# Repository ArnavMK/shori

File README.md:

**Shori PCB Layout:**

### What is this project?

Shori is a custom digital fx processor pcb for electric guitars. This is the heart of the modular project i am building called Wave forge (a solid state guitar amplifier )
And this is the first revision of the board!

This project comprises of three different printed circuit boards
1. Main power amp, preamp and I/O board: Shoyu (To be started)
2. The Digital FX processor: Shori (Rev 1 finished) 
3. The Screen controller board: Gamen (to be started)

here is the link for waveforge: [Here](https://github.com/ArnavMK/WaveForge)

### How to use it?

This is just rev 1 and is not manufactured yet, but this is a part of much larger multi board system and hence it needs to be connected to the other boards, through the two main connectors
The main ribbon connector for power and guitar audio from Shoyu. And the JST connector for the UART communication between the screen and shori. The screen has UI for controlling the parameters the digital fx like wet time modulation for delay and chorus. The screen will also have a waveform visualizer which is also be generated through shori.

### Why I made it

I have been playing electric for the past 11 years and never thought to build my own amp untill i met a friend profound in electronics and hardware design who inspired me into making my own. This board is the first step into putting a massive dent in WaveForge and i cant wait to finish it. Linked posts do not know what's coming for them.

I am pretty much nuking half the board for rev 2 now, after some peer roasting and friendly fire

### Project Pictures

There is no 3D encloser cad for shori yet! because that is the amp. Layout and 3D cad given on top of this page.

---

### Bill of Materials (BOM) FOR REV 1 ONLY !

This bom does not include the extra amount for each component, this is for only one shori board with perfect amount of compoenents!

*(A full `shori.csv` is also included in the root directory of this repository).*

| Component | Part Number | Quantity | Link | Cost (euro) |
| --- | --- | --- | --- | --- |
| Microcontroller | STM32F405RGT6 | 1 | [Link](https://www.digikey.ie/en/products/detail/stmicroelectronics/STM32F405RGT6/2754208) | 10.4 |
| Audio Codec | TI PCM3060 | 1 | [Link](https://www.digikey.com/en/models/1900019?tab=snapmagic) | 5.78 |
| Dual Audio Op-Amp | NE5532 | 1 | [Link](https://www.digikey.com/en/products/detail/texas-instruments/NE5532DR/499499) | 0.43 |
| Crystal Oscillator | 7M-25.000MAAE-T | 1 | [Link](https://www.digikey.ie/en/products/detail/txc-corporation/7M-25-000MAAE-T/3674351) | 0.59 |
| 3.3V LDO Regulator | AP2112K-3.3 | 1 | [Link](https://www.digikey.ie/en/products/detail/diodes-incorporated/ap2112k-3-3trg1/4470746) | 0.22 |
| 0805 capacitors (10uF) | 0805B475K160CC | 6 | [Link](https://www.digikey.com/en/products/detail/nextgen-components/0805B475K160CC/22601960?s=N4IgjCBcpgLFoDGUBmBDANgZwKYBoQB7KAbXAAYAOAdlgCYQBdAgBwBcoQBlNgJwEsAdgHMQAXwJhqCEMkjps%2BIqRD06sMAFYmrDpG58hoiSDqaG0Waky4CxSGXV0AnGEo6Q7TjwEjxk50pnGTkFW2UHEHImEzpyWGDLUJslezJyADowAAIAVoAxEAJYDOo8wslyco8vfQBVQX42AHkUAFkcNCwAV14cfxAAWngk60U7FVcANnJpRhNB7VH5FInIiHmxMSA) | 0.34 |
| 0805 capacitors (100nF) | 0805B104K500BD | 11 | [Link](https://www.digikey.com/en/products/detail/nextgen-components/0805B104K500BD/15776052) | 0.078 |
| Custom PCB | 4-Layer FR4 | 5 | [Link](https://jlcpcb.com/) | 6.02 |
| JLCPCB shipping | DHL to ireland | - | [Link](https://jlcpcb.com/) | 26.95 |
| 0805 capacitors (2.2uF) | CL21B225KAFNNNE | 2 | [Link](https://www.digikey.com/en/products/detail/samsung-electro-mechanics/CL21B225KAFNNNE/3888612) | 0.12 |
| 0805 capacitors (1uF) | CL21B105KAFNNNE | 3 | [Link](https://www.digikey.com/en/products/detail/samsung-electro-mechanics/CL21B105KAFNNNE/3886724) | 0.10 |
| 0805 resistors (10K) | CR0805-FX-1002ELF | 7 | [Link](https://www.digikey.com/en/products/detail/bourns-inc/CR0805-FX-1002ELF/3593209) | 0.10 |

total price is around 78.64 euros.

### Notes for rev2

---

- Use the CS4272 audio codec for easier layout and routing with better top and bottom clipping range!
- Divide the main IDC connector into three sperate connectors for POWER (5V in), AUDIO_IN and AUDIO_OUT
- Add via fence and clear division between the analog and digital domains
- Add filtering for the audio input and output to the codec for optimal performance.

Thank you!

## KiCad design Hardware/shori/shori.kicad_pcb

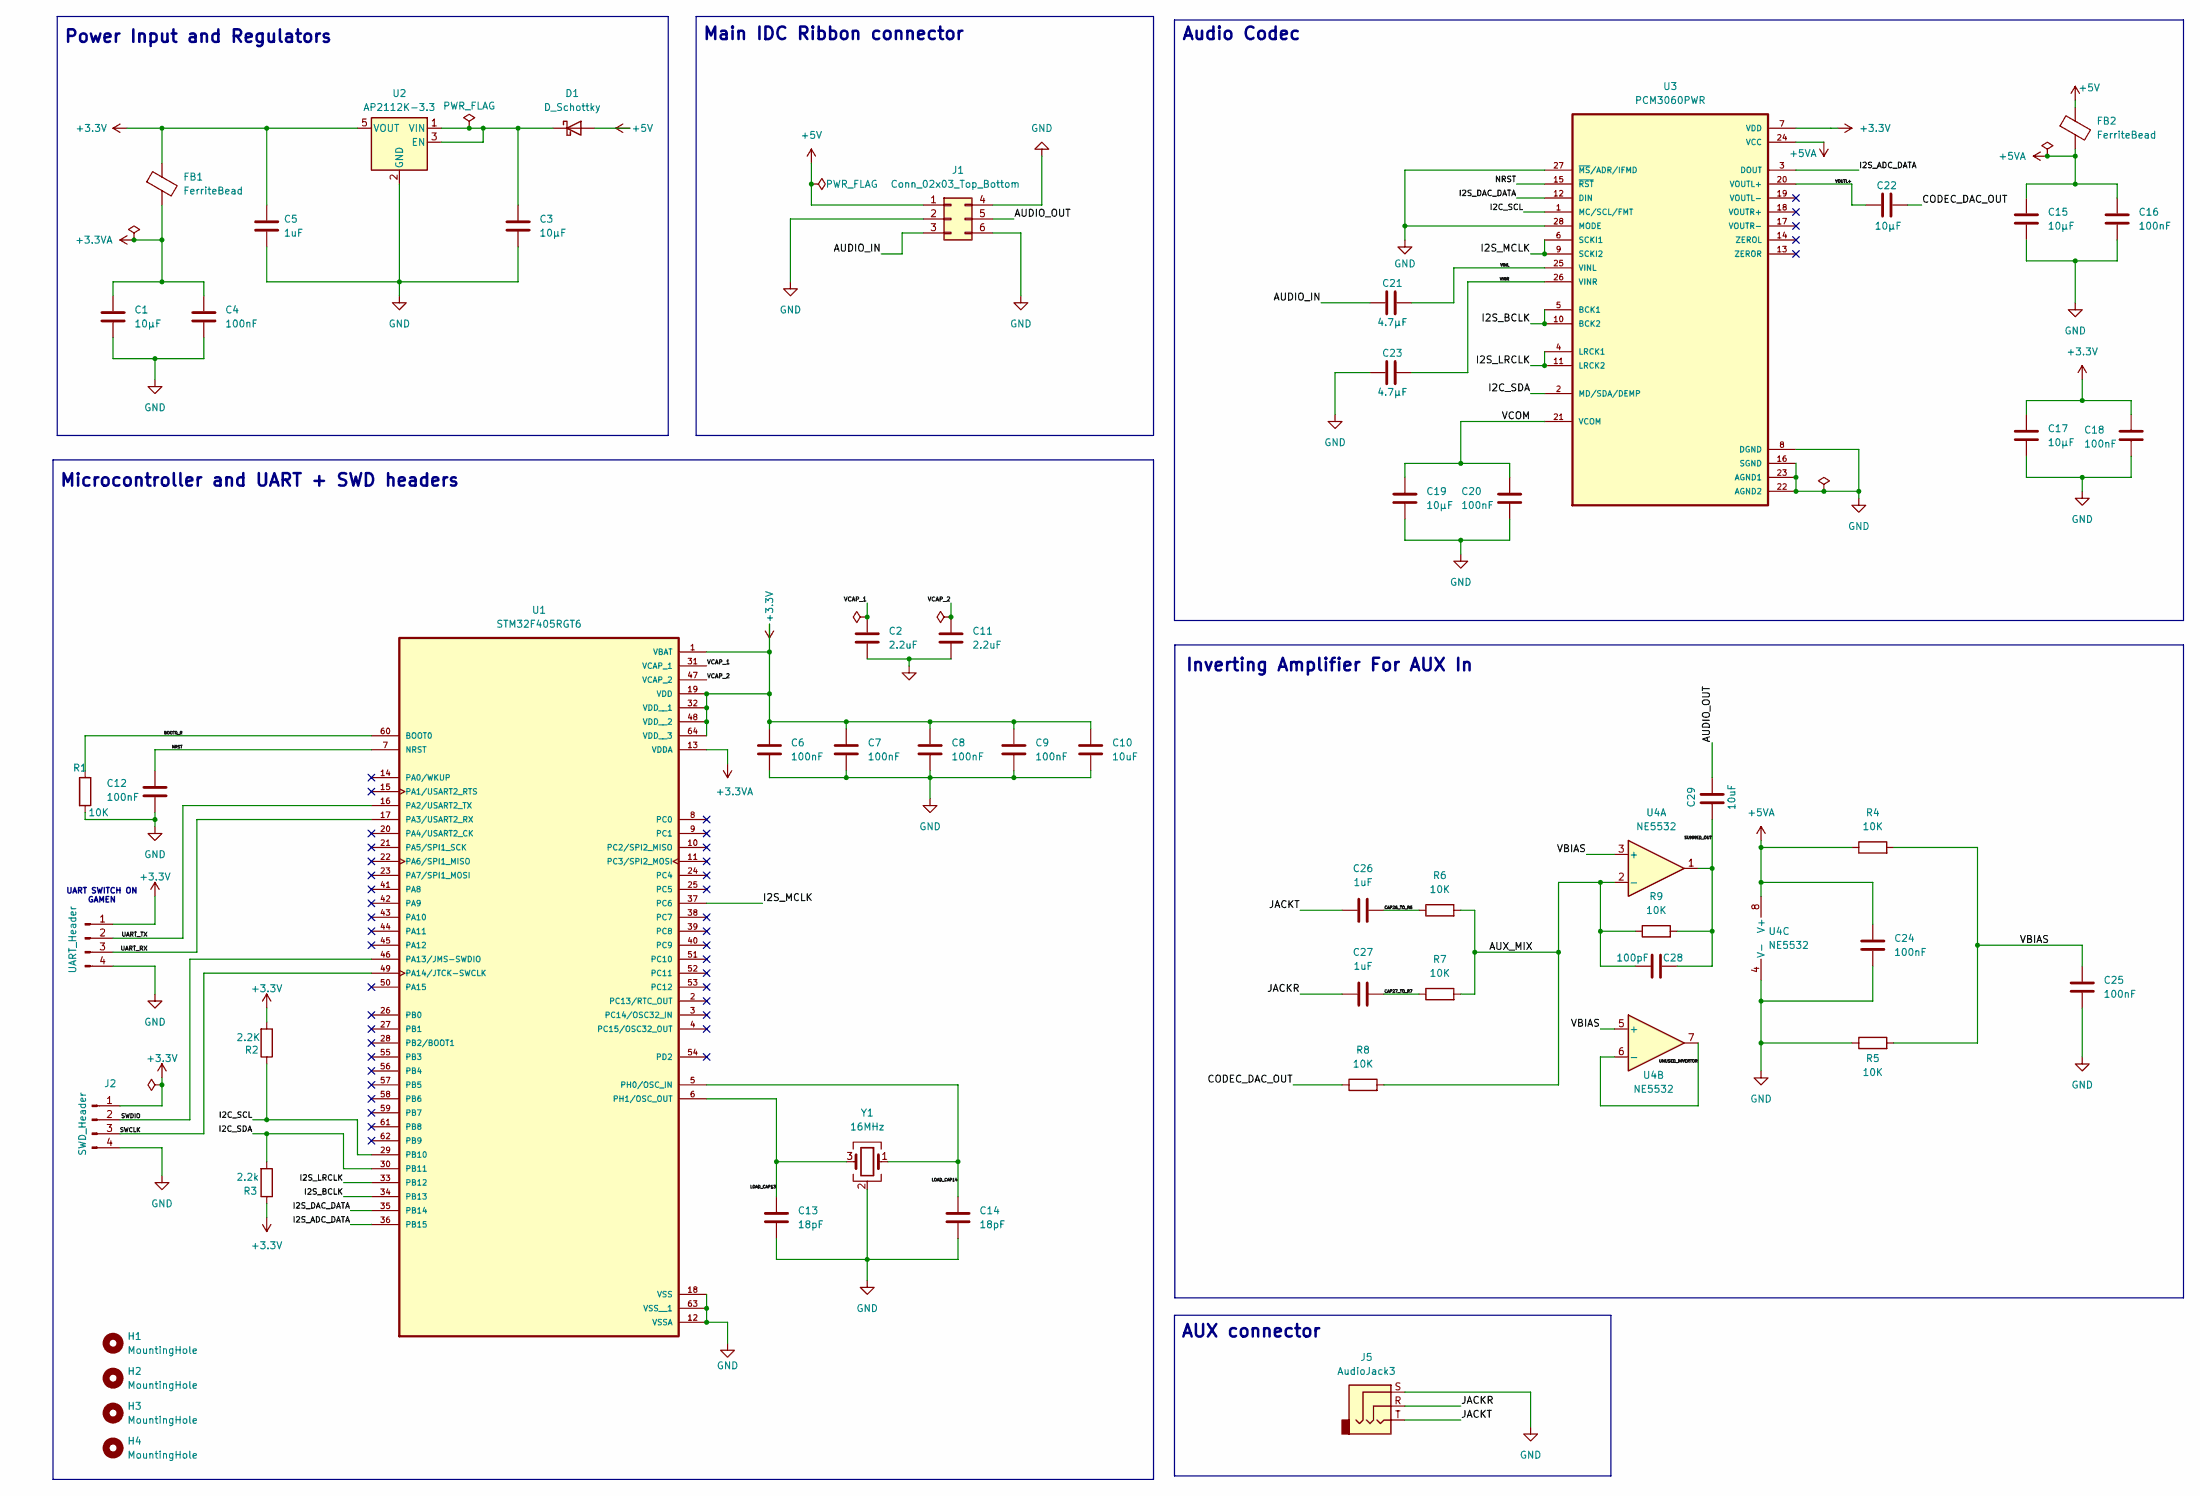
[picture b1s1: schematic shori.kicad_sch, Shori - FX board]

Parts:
C1: 10μF; C_0805_2012Metric
C2, C11: 2.2uF; C_0805_2012Metric
C3, C15, C17, C19, C22: 10μF; C_1206_3216Metric
C4, C6, C7, C8, C9, C12, C16, C18, C20, C24, C25: 100nF; C_0805_2012Metric
C5, C26, C27: 1uF; C_0805_2012Metric
C10, C29: 10uF; C_1206_3216Metric
C13, C14: 18pF; C_0805_2012Metric
C21, C23: 4.7μF; C_0805_2012Metric
C28: 100pF; C_0805_2012Metric
D1: D_Schottky; D_SOD-123
FB1, FB2: FerriteBead; L_0805_2012Metric
H1, H2, H3, H4: MountingHole; MountingHole_3mm
J1: Conn_02x03_Top_Bottom; IDC-Header_2x03_P2.54mm_Vertical
J2: SWD_Header; PinHeader_1x04_P2.54mm_Vertical
J3: UART_Header; JST_XH_B4B-XH-A_1x04_P2.50mm_Vertical
J5: AudioJack3; Jack_3.5mm_CUI_SJ1-3523N_Horizontal
R1, R4, R5, R6, R7, R8, R9: 10K; R_0805_2012Metric
R2: 2.2K; R_0805_2012Metric
R3: 2.2k; R_0805_2012Metric
U1: STM32F405RGT6; QFP50P1200X1200X160-64N; PARTREV LTR
U2: AP2112K-3.3; SOT-23-5
U3: PCM3060PWR; SOP65P640X120-28N
U4: NE5532; SOIC-8_3.9x4.9mm_P1.27mm
Y1: 16MHz; Crystal_SMD_3225-4Pin_3.2x2.5mm_HandSoldering

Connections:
+3.3V: C5.1, C6.1, C7.1, C8.1, C9.1, C10.1, C17.1, C18.1, FB1.1, J2.1, J3.1, R2.2, R3.1, U1.1 (VBAT), U1.19 (VDD), U1.32 (VDD__1), U1.48 (VDD__2), U1.64 (VDD__3), U2.5 (VOUT), U3.7 (VDD); also elsewhere on the board
+3.3VA: C1.1, C4.1, FB1.2, U1.13 (VDDA)
+5V: D1.2 (A), FB2.1, J1.1; also elsewhere on the board
+5VA: C15.1, C16.1, C24.1, FB2.2, R4.1, U3.24 (VCC), U4.8 (V+)
/AUDIO_IN: C21.2, J1.3; also elsewhere on the board
/AUDIO_OUT: C29.2, J1.5; also elsewhere on the board
/AUX_MIX: C28.1, R6.2, R7.2, R8.2, R9.1, U4.2 (-)
/BOOT0_R: R1.1, U1.60 (BOOT0)
/CAP26_TO_R6: C26.2, R6.1
/CAP27_TO_R7: C27.2, R7.1
/CODEC_DAC_OUT: C22.2, R8.1
/I2C_SCL: R2.1, U1.29 (PB10), U3.1 (MC/SCL/FMT)
/I2C_SDA: R3.2, U1.30 (PB11), U3.2 (MD/SDA/DEMP)
/I2S_ADC_DATA: U1.36 (PB15), U3.3 (DOUT)
/I2S_BCLK: U1.34 (PB13), U3.5 (BCK1), U3.10 (BCK2)
/I2S_DAC_DATA: U1.35 (PB14), U3.12 (DIN)
/I2S_LRCLK: U1.33 (PB12), U3.4 (LRCK1), U3.11 (LRCK2)
/I2S_MCLK: U1.37 (PC6), U3.6 (SCKI1), U3.9 (SCKI2)
/JACKR: C27.1, J5.R; also elsewhere on the board
/JACKT: C26.1, J5.T; also elsewhere on the board
/LOAD_CAP13: C13.1, U1.6 (PH1/OSC_OUT), Y1.3
/LOAD_CAP14: C14.1, U1.5 (PH0/OSC_IN), Y1.1
/NRST: C12.1, U1.7 (NRST), U3.15 (~RST)
/SUMMED_OUT: C28.2, C29.1, R9.2, U4.1
/SWCLK: J2.3, U1.49 (PA14/JTCK-SWCLK); also elsewhere on the board
/SWDIO: J2.2, U1.46 (PA13/JMS-SWDIO); also elsewhere on the board
/UART_RX: J3.3, U1.17 (PA3/USART2_RX); also elsewhere on the board
/UART_TX: J3.2, U1.16 (PA2/USART2_TX); also elsewhere on the board
/UNUSED_INVERTOR: U4.6 (-), U4.7
/VBIAS: C25.1, R4.2, R5.2, U4.3 (+), U4.5 (+)
/VCAP_1: C2.2, U1.31 (VCAP_1)
/VCAP_2: C11.2, U1.47 (VCAP_2)
/VCOM: C19.1, C20.1, U3.21 (VCOM)
/VINL: C21.1, U3.25 (VINL)
/VINR: C23.1, U3.26 (VINR)
/VOUTL+: C22.1, U3.20 (VOUTL+)
GND: C1.2, C2.1, C3.2, C4.2, C5.2, C6.2, C7.2, C8.2, C9.2, C10.2, C11.1, C12.2, C13.2, C14.2, C15.2, C16.2, C17.2, C18.2, C19.2, C20.2, C23.2, C24.2, C25.2, J1.2, J1.4, J1.6, J2.4, J3.4, J5.S, R1.2, R5.1, U1.12 (VSSA), U1.18 (VSS), U1.63 (VSS__1), U2.2 (GND), U3.8 (DGND), U3.16 (SGND), U3.22 (AGND2), U3.23 (AGND1), U3.27 (~MS/ADR/IFMD), U3.28 (MODE), U4.4 (V-), Y1.2 (G), Y1.4 (G); also elsewhere on the board
unnamed: C3.1, D1.1 (K), U2.1 (VIN), U2.3 (EN)

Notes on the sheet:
Audio Codec
Inverting Amplifier For AUX In
Microcontroller and UART + SWD headers
Power Input and Regulators
Main IDC Ribbon connector
UART SWITCH ON GAMEN
AUX connector

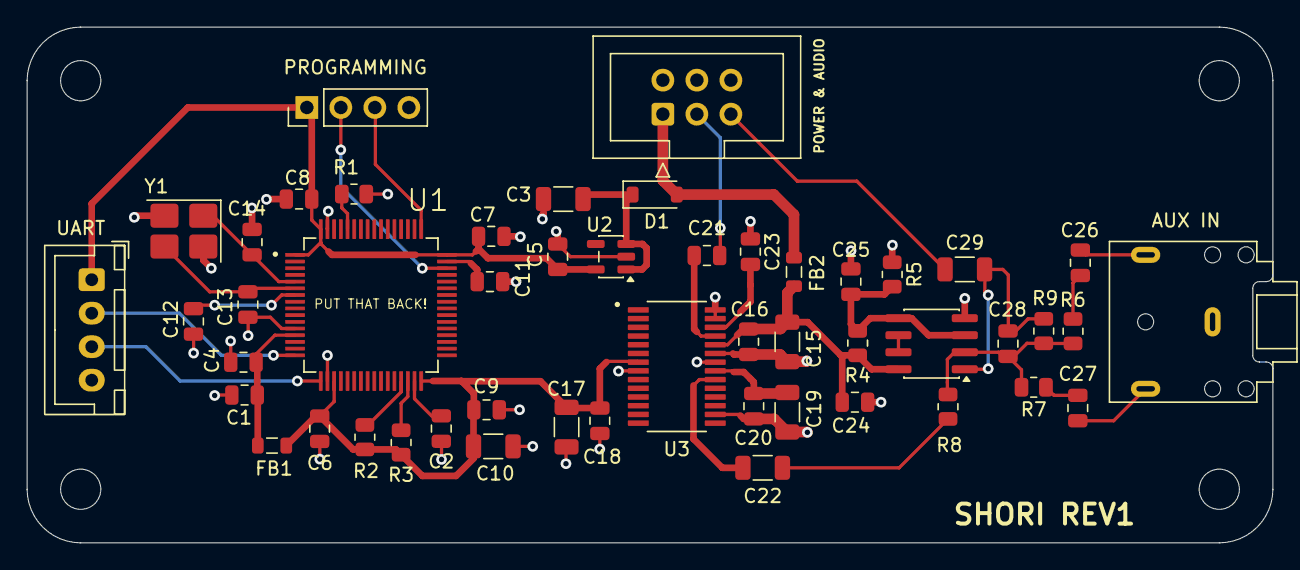
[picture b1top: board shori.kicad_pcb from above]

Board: 4 copper layers, 93.0 x 38.5 mm, 54 parts (0 on the bottom side), 38 nets.

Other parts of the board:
AUX IN: AudioJack3; Jack_3.5mm_CUI_SJ1-3523N_Horizontal
POWER & AUDIO: Conn_02x03_Top_Bottom; IDC-Header_2x03_P2.54mm_Vertical
PROGRAMMING: SWD_Header; PinHeader_1x04_P2.54mm_Vertical
UART: UART_Header; JST_XH_B4B-XH-A_1x04_P2.50mm_Vertical

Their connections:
+3.3V: PROGRAMMING.1, UART.1; also elsewhere on the board
+5V: POWER & AUDIO.1; also elsewhere on the board
/AUDIO_IN: POWER & AUDIO.3; also elsewhere on the board
/AUDIO_OUT: POWER & AUDIO.5; also elsewhere on the board
/JACKR: AUX IN.R; also elsewhere on the board
/JACKT: AUX IN.T; also elsewhere on the board
/SWCLK: PROGRAMMING.3; also elsewhere on the board
/SWDIO: PROGRAMMING.2; also elsewhere on the board
/UART_RX: UART.3; also elsewhere on the board
/UART_TX: UART.2; also elsewhere on the board
GND: AUX IN.S, POWER & AUDIO.2, POWER & AUDIO.4, POWER & AUDIO.6, PROGRAMMING.4, UART.4; also elsewhere on the board

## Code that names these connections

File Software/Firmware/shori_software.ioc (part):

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Mcu.Name=STM32F405RGTx
Mcu.Package=LQFP64
Mcu.UserName=STM32F405RGTx
PB10.Mode=I2C
PB10.Signal=I2C2_SCL
PB11.Mode=I2C
PB11.Signal=I2C2_SDA
PB12.Mode=Full_Duplex_Master
PB12.Signal=I2S2_WS
PB13.Mode=Full_Duplex_Master
PB13.Signal=I2S2_CK
PB14.Mode=Full_Duplex_Master
PB14.Signal=I2S2_ext_SD
PB15.Mode=Full_Duplex_Master
PB15.Signal=I2S2_SD
PC6.Mode=Master_Clock_Activated
PC6.Signal=I2S2_MCK
PH0-OSC_IN.Mode=HSE-External-Oscillator
PH0-OSC_IN.Signal=RCC_OSC_IN
PH1-OSC_OUT.Mode=HSE-External-Oscillator
PH1-OSC_OUT.Signal=RCC_OSC_OUT
RCC.HSE_VALUE=25000000
RCC.SYSCLKFreq_VALUE=16000000
board=custom

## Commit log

2026-03-06 imported shori from waveforge
2026-03-06 Initialize README with project overview and BOM
    Added project details, BOM, and notes for revision 2.
2026-03-06 Images in readme
